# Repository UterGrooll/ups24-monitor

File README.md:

# UPS 24V Monitor

Контроллер мониторинга ИБП **Штиль PS2420G** на Arduino Nano: измерение напряжения шины 24 В, температуры АКБ и состояния двух сухих контактов. Данные передаются по UART на внешний контроллер для дальнейшего опроса из SCADA.

## Возможности

- Один канал измерения напряжения **0…30 В**.
- Внешний датчик температуры **DS18B20**.
- Два входа сухих контактов через **PC817** с LED-индикацией.
- Выход **UART 9600 бод**, значения в целочисленном формате.
- Питание через понижающий модуль **LM2596S**, выход 5 В.
- Корпусной индикатор напряжения и съёмный выключатель.
- Плата KiCad для одностороннего травления; корпус FreeCAD и файлы 3D-печати.

> Эта плата сама не реализует Modbus TCP и не подключается к Ethernet.
> UART принимает отдельный контроллер-шлюз. Два контакта ИБП не означают два независимых канала измерения напряжения — АЦП-канал здесь один.

## Аппаратная часть

| Узел | Исполнение |
| --- | --- |
| Контроллер | Arduino Nano, ATmega328P, логика 5 В |
| Питание | Шина ИБП около 27 В → LM2596S → 5 В |
| Делитель | 30 кОм + 30 кОм / 10 кОм, номинальный коэффициент 7 |
| Температура | DS18B20, трёхпроводное подключение |
| Дискретные входы | 2 × PC817 |
| Интерфейс | Однонаправленный TTL UART |
| Проект платы | KiCad 10 |
| Корпус | FreeCAD, 3MF |

### Выводы Nano

| Сигнал | Пин |
| --- | --- |
| Напряжение через делитель | A0 |
| DS18B20 DATA | D7 |
| Контакт ИБП 1 | D6 |
| Контакт ИБП 2 | D5 |
| UART TX | D1/TX |
| Общий провод | GND |

D0/RX для текущей прошивки не используется. Пины относятся к **измерительной Nano**, не к внешнему ПАК.

## Фотографии

| Плата | Проверка UART |
| --- | --- |
|  |  |

| Разводка | Корпус |
| --- | --- |
|  |  |

[Все фотографии и изображения](docs/images/) взяты из материалов сборки. Фото и скриншоты могут отражать промежуточные этапы; перед изготовлением сверяйте их с исходниками KiCad.

## Прошивка

Скетч: [firmware/KP_24V/KP_24V.ino](firmware/KP_24V/KP_24V.ino).

1. Открыть скетч в Arduino IDE.
2. Установить библиотеку **GyverDS18**.
3. Выбрать Arduino Nano и загрузчик, соответствующий установленной плате.
4. Проверить безопасное питание при USB-подключении, затем загрузить скетч.
5. Открыть монитор порта на **9600 бод**.

Библиотеки Ethernet и ModbusTCP_RU на этой Nano не требуются. Логика существующего скетча при подготовке репозитория не изменялась.

### Калибровка напряжения

В скетче сохранена двухточечная калибровка конкретного макета:

| Входное напряжение | Значение АЦП |
| --- | ---: |
| 5,0 В | 144 |
| 30,0 В | 880 |

Константы `VOLTAGE_CAL_LOW_DV = 50` и `VOLTAGE_CAL_HIGH_DV = 300` заданы в десятых долях вольта. Для другой платы и источника 5 В нужно повторить измерения и изменить калибровку. Шаг вывода 0,1 В не означает гарантированную точность 0,1 В.

## UART и SCADA

Пример потока:

```text
V:270
T:234
C1:0
C2:1
```

Это 27,0 В, 23,4 °C, нормальное состояние ИБП 1 и авария/размыкание контакта ИБП 2.

Полный формат, подключение и различия карт регистров внешних приёмников описаны в [docs/uart.md](docs/uart.md).

Для стендового Modbus TCP-приёмника используется отдельный проект [SCADA Modbus TCP Relay Timer](https://github.com/UterGrooll/scada-modbus-tcp-relay-timer) на базе [ModbusTCP_RU](https://github.com/UterGrooll/ModbusTCP_RU). Исходники этого приёмника не включены в данный репозиторий.

## Схема, плата и корпус

Нажмите на схему, чтобы открыть изображение в полном размере.

- [Проект KiCad](schematic/KP_24V/KP_24V.kicad_pro)
- [Принципиальная схема](schematic/KP_24V/KP_24V.kicad_sch)
- [Печатная плата](schematic/KP_24V/KP_24V.kicad_pcb)
- [Примечания по аппаратной части](schematic/KP_24V/README_CONTROLLER_RU.md)
- [Модель корпуса FreeCAD](case/case.FCStd)
- [Основание для печати](case/case-Body.3mf)
- [Крышка для печати](case/case-крышка.3mf)

Локальные библиотеки символов и посадочных мест сохранены рядом с KiCad-проектом; пути используют `${KIPRJMOD}`.

## Ограничения и безопасное подключение

- Перед установкой Nano настроить DC/DC на **5,00 В**. Не подавать 24–30 В непосредственно на вывод 5V или A0.
- Для USB Nano отключить внешние 24 В и снять **JP1** между OUT+ DC/DC и шиной +5 В. Проверить, что джампер действительно разрывает эту цепь на собранной плате.
- Перед изменением соединений отключить все источники питания, включая USB. Подпитка возможна и через сигнальные линии.
- PC817 не обеспечивает развязку всего устройства: GND питания, Nano и UART общий.
- UART рассчитан на короткое соединение; линия не является RS-232 или RS-485.
- В текущем скетче нет антидребезга контактов. После потери DS18B20 повторный запуск измерений не гарантирован: внешний приёмник должен контролировать свежесть каждого канала.
- Это авторский прототип мониторинга, а не устройство защиты АКБ или сертифицированный промышленный контроллер.

## Структура

```text
firmware/KP_24V/     Прошивка измерительной Nano
schematic/KP_24V/    KiCad: схема, PCB, локальные библиотеки
case/               FreeCAD и файлы корпуса
docs/images/        Фотографии и скриншоты сборки
docs/uart.md        Формат UART и интеграция
```

Резервные копии CAD, локальная история, старые отчёты, Word-документы и материалы «Подключение» исключены из Git.

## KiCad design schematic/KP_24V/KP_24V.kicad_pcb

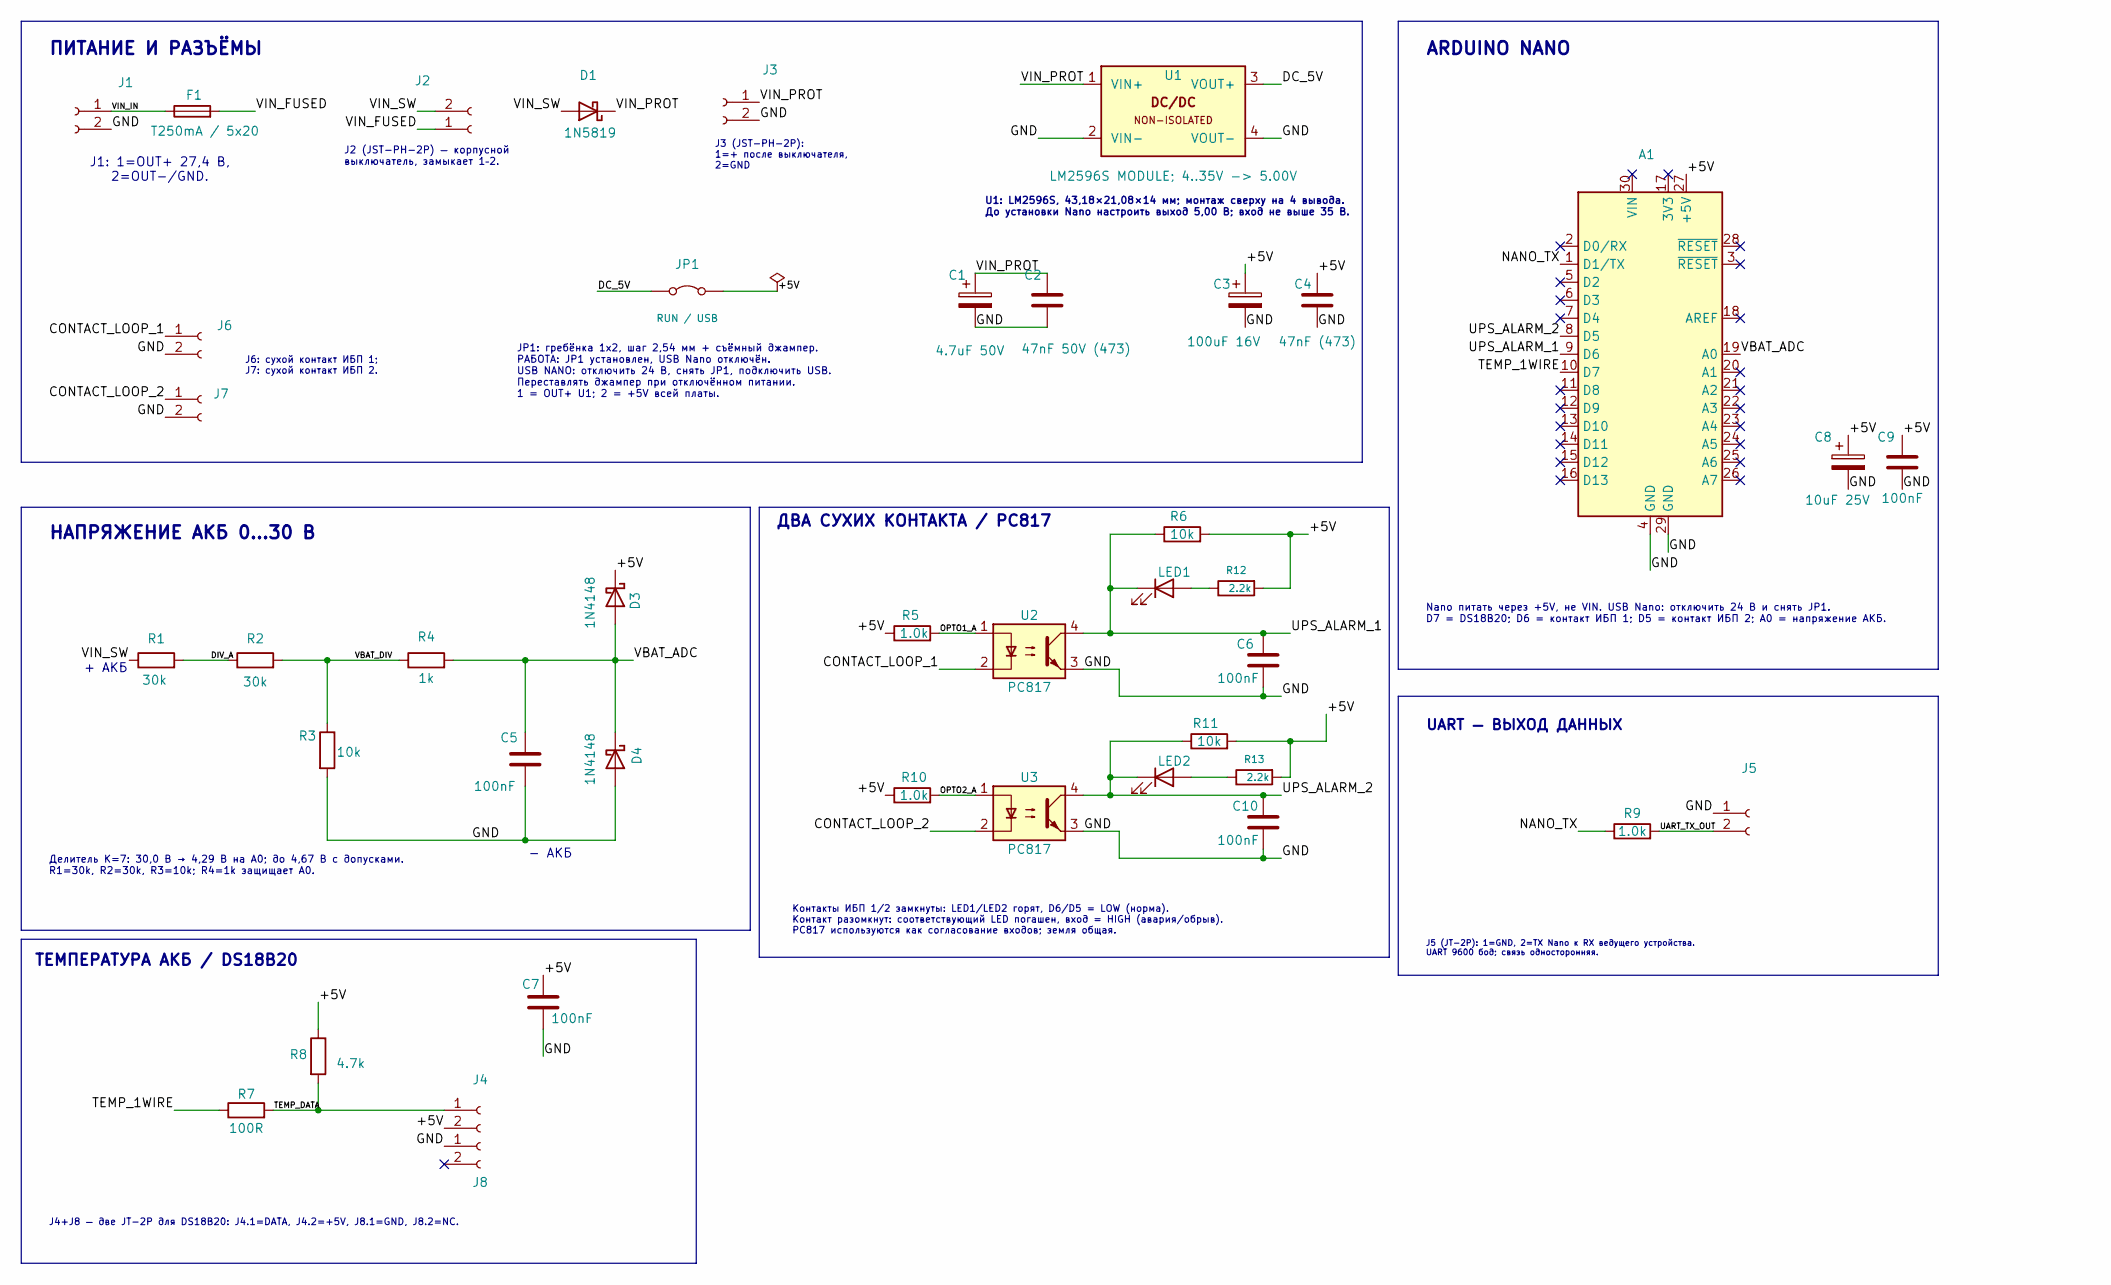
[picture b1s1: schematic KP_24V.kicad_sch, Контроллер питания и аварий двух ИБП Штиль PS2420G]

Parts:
A1: Arduino Nano / ATmega328P (5V); Arduino_Nano
C1: 4.7uF 50V; C_Radial_D5.0mm_H11.0mm_P2.00mm
C2: 47nF 50V (473); C_Disc_D5.0mm_W2.5mm_P5.00mm
C3: 100uF 16V; C_Radial_D5.0mm_H11.0mm_P2.00mm
C4: 47nF (473); C_Disc_D5.0mm_W2.5mm_P5.00mm
C5, C6, C7, C9, C10: 100nF; C_Disc_D5.0mm_W2.5mm_P5.00mm
C8: 10uF 25V; C_Radial_D4.0mm_H7.0mm_P1.50mm
D1: 1N5819; D_DO-41_SOD81_P10.16mm_Horizontal
D3, D4: 1N4148; D_DO-35_SOD27_P7.62mm_Horizontal
F1: T250mA / 5x20; Fuseholder_Clip-5x20mm_Littelfuse_111_Inline_P20.00x5.00mm_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
J1: JT-2P / ПИТАНИЕ 24V; TerminalBlock_Phoenix_MKDS-1,5-2-5.08_1x02_P5.08mm_Horizont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
J2: JST-PH-2P / ВЫКЛЮЧАТЕЛЬ; JST_PH_B2B-PH-K_1x02_P2.00mm_Vertical
J3: JST-PH-2P / ИНДИКАТОР 12..72V; JST_PH_B2B-PH-K_1x02_P2.00mm_Vertical
J4: JT-2P / DS18B20 DATA+5V; TerminalBlock_Phoenix_MKDS-1,5-2-5.08_1x02_P5.08mm_Horizont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
J5: JT-2P / UART OUT; TerminalBlock_Phoenix_MKDS-1,5-2-5.08_1x02_P5.08mm_Horizont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
J6: JT-2P / СУХОЙ КОНТАКТ ИБП 1; TerminalBlock_Phoenix_MKDS-1,5-2-5.08_1x02_P5.08mm_Horizont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
J7: JT-2P / СУХОЙ КОНТАКТ ИБП 2; TerminalBlock_Phoenix_MKDS-1,5-2-5.08_1x02_P5.08mm_Horizont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
J8: JT-2P / DS18B20 GND+NC; TerminalBlock_Phoenix_MKDS-1,5-2-5.08_1x02_P5.08mm_Horizont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
JP1: RUN / USB; PinHeader_1x02_P2.54mm_Vertical
LED1, LED2: LED (НОРМА); LED_D5.0mm_Clear
R1, R2: 30k; R_Axial_DIN0207_L6.3mm_D2.5mm_P10.16mm_Horizontal
R3, R6, R11: 10k; R_Axial_DIN0207_L6.3mm_D2.5mm_P10.16mm_Horizontal
R4: 1k; R_Axial_DIN0207_L6.3mm_D2.5mm_P10.16mm_Horizontal
R5, R9, R10: 1.0k; R_Axial_DIN0207_L6.3mm_D2.5mm_P10.16mm_Horizontal
R7: 100R; R_Axial_DIN0207_L6.3mm_D2.5mm_P10.16mm_Horizontal
R8: 4.7k; R_Axial_DIN0207_L6.3mm_D2.5mm_P10.16mm_Horizontal
R12, R13: 2.2k; R_Axial_DIN0207_L6.3mm_D2.5mm_P10.16mm_Horizontal; PartNumber RC0805FR-07510RL
U1: LM2596S MODULE; 4..35V -> 5.00V; LM2596S_Module_43x21_P40x17
U2, U3: PC817; DIP-4_W7.62mm

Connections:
/+5V: A1.27 (+5V), C3.1, C4.1, C7.1, C8.1, C9.1, D3.1 (K), J4.2, JP1.2 (B), R5.1, R6.2, R8.1, R10.1, R11.2, R12.2, R13.2
/CONTACT_LOOP_1: J6.1, U2.2
/CONTACT_LOOP_2: J7.1, U3.2
/DC_5V: JP1.1 (A), U1.3 (VOUT+)
/DIV_A: R1.2, R2.1
/GND: A1.4 (GND), A1.29 (GND), C1.2, C2.2, C3.2, C4.2, C5.2, C6.2, C7.2, C8.2, C9.2, C10.2, D4.2 (A), J1.2, J3.2, J5.1, J6.2, J7.2, J8.1 (Pin_1_1), R3.2, U1.2 (VIN-), U1.4 (VOUT-), U2.3, U3.3
/NANO_TX: A1.1 (D1/TX), R9.1
/OPTO1_A: R5.2, U2.1
/OPTO2_A: R10.2, U3.1
/TEMP_1WIRE: A1.10 (D7), R7.1
/TEMP_DATA: J4.1, R7.2, R8.2
/UART_TX_OUT: J5.2, R9.2
/UPS_ALARM_1: A1.9 (D6), C6.1, LED1.1 (K), R6.1, U2.4
/UPS_ALARM_2: A1.8 (D5), C10.1, LED2.1 (K), R11.1, U3.4
/VBAT_ADC: A1.19 (A0), C5.1, D3.2 (A), D4.1 (K), R4.2
/VBAT_DIV: R2.2, R3.1, R4.1
/VIN_FUSED: F1.2, J2.1
/VIN_IN: F1.1, J1.1
/VIN_PROT: C1.1, C2.1, D1.1 (K), J3.1, U1.1 (VIN+)
/VIN_SW: D1.2 (A), J2.2, R1.1
unnamed: LED1.2 (A), R12.1
unnamed: LED2.2 (A), R13.1

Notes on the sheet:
ТЕМПЕРАТУРА АКБ / DS18B20
Контакты ИБП 1/2 замкнуты: LED1/LED2 горят, D6/D5 = LOW (норма). Контакт разомкнут: соответствующий LED погашен, вход = HIGH (авария/обрыв). PC817 используются как согласование входов; земля общая.
J5 (JT-2P): 1=GND, 2=TX Nano к RX ведущего устройства. UART 9600 бод; связь односторонняя.
Nano питать через +5V, не VIN. USB Nano: отключить 24 В и снять JP1. D7 = DS18B20; D6 = контакт ИБП 1; D5 = контакт ИБП 2; A0 = напряжение АКБ.
Делитель K=7: 30,0 В → 4,29 В на A0; до 4,67 В с допусками. R1=30k, R2=30k, R3=10k; R4=1k защищает A0.
J4+J8 — две JT-2P для DS18B20: J4.1=DATA, J4.2=+5V, J8.1=GND, J8.2=NC.
+ АКБ
J3 (JST-PH-2P): 1=+ после выключателя, 2=GND
UART — ВЫХОД ДАННЫХ
J2 (JST-PH-2P) — корпусной выключатель, замыкает 1–2.
ARDUINO NANO
ДВА СУХИХ КОНТАКТА / PC817
- АКБ
U1: LM2596S, 43,18×21,08×14 мм; монтаж сверху на 4 вывода. До установки Nano настроить выход 5,00 В; вход не выше 35 В.
JP1: гребёнка 1x2, шаг 2,54 мм + съёмный джампер. РАБОТА: JP1 установлен, USB Nano отключён. USB NANO: отключить 24 В, снять JP1, подключить USB. Переставлять джампер при отключённом питании. 1 = OUT+ U1; 2 = +5V всей платы.
НАПРЯЖЕНИЕ АКБ 0…30 В
ПИТАНИЕ И РАЗЪЁМЫ
J1: 1=OUT+ 27,4 В, 2=OUT−/GND.
J6: сухой контакт ИБП 1; J7: сухой контакт ИБП 2.

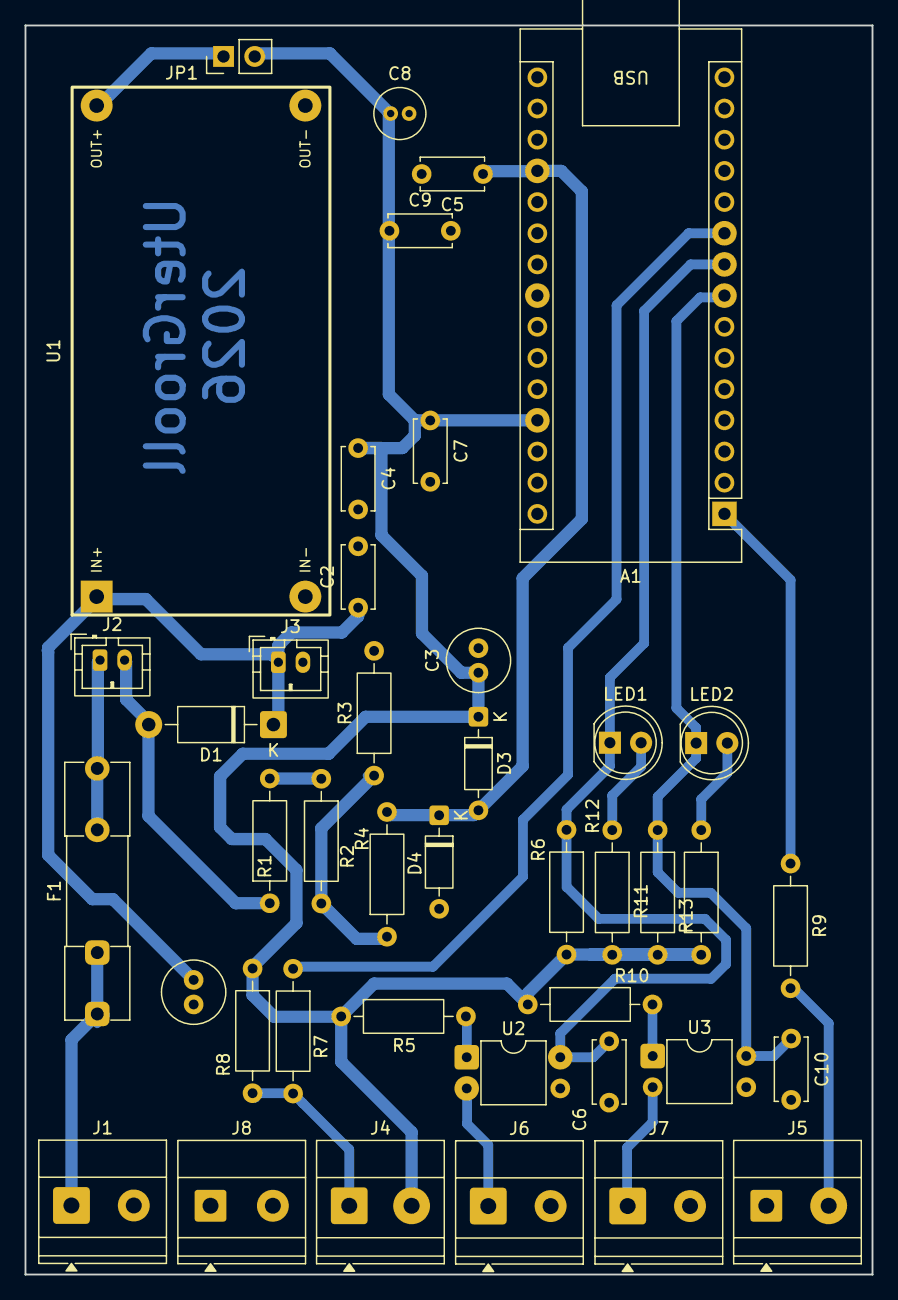
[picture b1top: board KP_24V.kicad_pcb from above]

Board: 2 copper layers, 69.0 x 101.8 mm, 42 parts (0 on the bottom side), 22 nets.
